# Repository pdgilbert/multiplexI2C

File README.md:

# multiplexI2C
Eight 4-position screw connectors on multiplexed on I2C with PCA9548A. 
This allows connecting 8 I2C sensors such as AHT10 (on module boards) using 
low voltage 4-wire cable.

##  Status: Working Prototype.

## Summary

Kicad project WIP.

PCB design to connect multiple (up to 8) I2C sensors (eg. AHT20) to a I2C multiplexer
connecting to an MCU. Sensor connectors are  4-pin KF128-2.54-4P generic screw terminals.
Many types of I2C sensors are inexpensive and easily available on module boards, 
but 4-wire cable will typically need to be attached. 

The pcb board has a LoRa radio on a SPI bus which transmits measurement results.
There is also a I2C header for an optional OLED display, intended mainly for debugging.

Related software is in repository https://github.com/pdgilbert/SensorProject_th8.

As of December 2025, this repository has three important branches. (Branch `main` is not 
an important branch but rather a somewhat stable version of the most active
development, which is on the `dev` branch. Both may be removed or reorganized 
in the future.)
 
Branch `blackpill-socket` has two 20-pin sockets arranged for a commonly available 
blackpill module. It has an RFM95 LoRa radio on spi, an I2C pinsocket arrange to plug in 
an SSD module for display, and 8 4-pin terminals multiplexed to connect I2C devices.
The pinsocket arrangement can also be used for jumper-wiring MCUs on other development
boards. Further work on this branch will be limited.
 
Branch `f411-RFM95W-module` has a footprint for a module with an MCU and LoRa radio.
(See repository MCU-LoRa for module details.)
It has a socket for I2C arranged to plug in an SSD module for display, 
and 8 4-pin terminals multiplexed to connect I2C devices. 
As of November 2025 this branch is almost ready to manufacture a prototype.
 
Branch `f411-RFM95W` has an STM32F411 MCU and RFM95W LoRa radio on the board (no module).
It has a socket for I2C arrange to plug in an SSD module for display, 
and 8 4-pin terminals multiplexed to connect I2C devices. 
As of December 2025 this branch is almost ready to manufacture a prototype.

See history further below for regarding status and testing of each branch.

Graphics below will be different on different branches, reflecting the differences above.
The `.png` files below are produced from kicad  in the `3D Viewer`  
with `File > Export Current View as PNG`.

( hints from https://docs.github.com/en/repositories/working-with-files/using-files/working-with-non-code-files#3d-file-viewer )

3D  `.wrl` file opens with Meshlab. Good, full colour. 
The file needs to be load into a viewer (e.g.
https://3dviewer.net/#model=https://github.com/pdgilbert/multiplexI2C/f411-RFM95W/Graphics/multiplexI2C.wrl )
or downloaded and viewed with your own viewer. 
To download go to the file in the Graphics/ directory and click on the file.
Github will try to render this, but fails because it is too large.
Then click on the download raw file icon at the top right. 
The file is produced from kicad  with `File > Export ... >  VRML...`

https://3dviewer.net/#model=https://github.com/pdgilbert/multiplexI2C/blob/f411-RFM95W/Graphics/multiplexI2C.wrl

3D  `.step` file can be loaded by Freecad. 
It can be load into a viewer (e.g. 
https://3dviewer.net/#model=https://github.com/pdgilbert/multiplexI2C/f411-RFM95W/Graphics/multiplexI2C.step)
or downloaded as above for `.wrl`.
The file is produced from kicad  with `File > Export ... >  STEP...`

3D  `.stl` file can be  rendered by Github, Meshlab and Freecad. So far only mono-colour is working. 
It can be load into a viewer (e.g. 
https://3dviewer.net/#model=https://github.com/pdgilbert/multiplexI2C/f411-RFM95W/Graphics/multiplexI2C.stl)
To render by Meshlab or Freecad requires downloading as above for `.wrl`.
The file is best produced by exporting a `.wrl` or `.step` file from kicad and
importing that to Meshlab or Freecad, and then exporting an `.stl` file.
The file can also be produced from kicad  with `File > Export ... >  STEP.../STEP...` but
the result has bad artifacts. The .wrl version is much better than the .stl version.

3D  `.ast` file (ASCII stl) is rendered by Github, according to above link, but files  
larger than 10 MB are too big for GitHub to display. 
The `multiplexI2C.ast` is almost 20MB so this format cannot be used by Github.
It is not rendered by Meshlab.

## History
 
 - `th8-F411` version `0.3.1 2025-12` (branch `f411-RFM95W`) has stm32f411 MCU chip and HopeRF RFM95W.
    This version is switched to ssd on I2C1 and sensors on I2C2, so it is consistent with SensorProject_t16.
    The software has a flag to indicate previous old versions.

 - `th8-F411` version `0.3.1M 2025-12` (branch `f411-RFM95W-module`) has not been manufactured/tested.

 - Version `0.1.1 2025-01` (branch `blackpill-socket`) has pull up resistor added but 
   has not been manufactured/tested. This version has ssd on I2C2 and sensors on I2C1.

 - Version `0.1.0 2024-09` (branch `blackpill-socket`) needs manual addition of a pull up 
   resistor to nss of the RFM95W radio module, MCU pin A4. 
   With this modification it works with `blackpill` `stm32f401` or `stm32f411` inserted,
   using AHT10 and AHT20 sensors. With jumper wiring it has also been used to test a WeAct 
   Studio STM32474G474 board.  This version has ssd on I2C2 and sensors on I2C1.
   See notes re testing in the software repository.

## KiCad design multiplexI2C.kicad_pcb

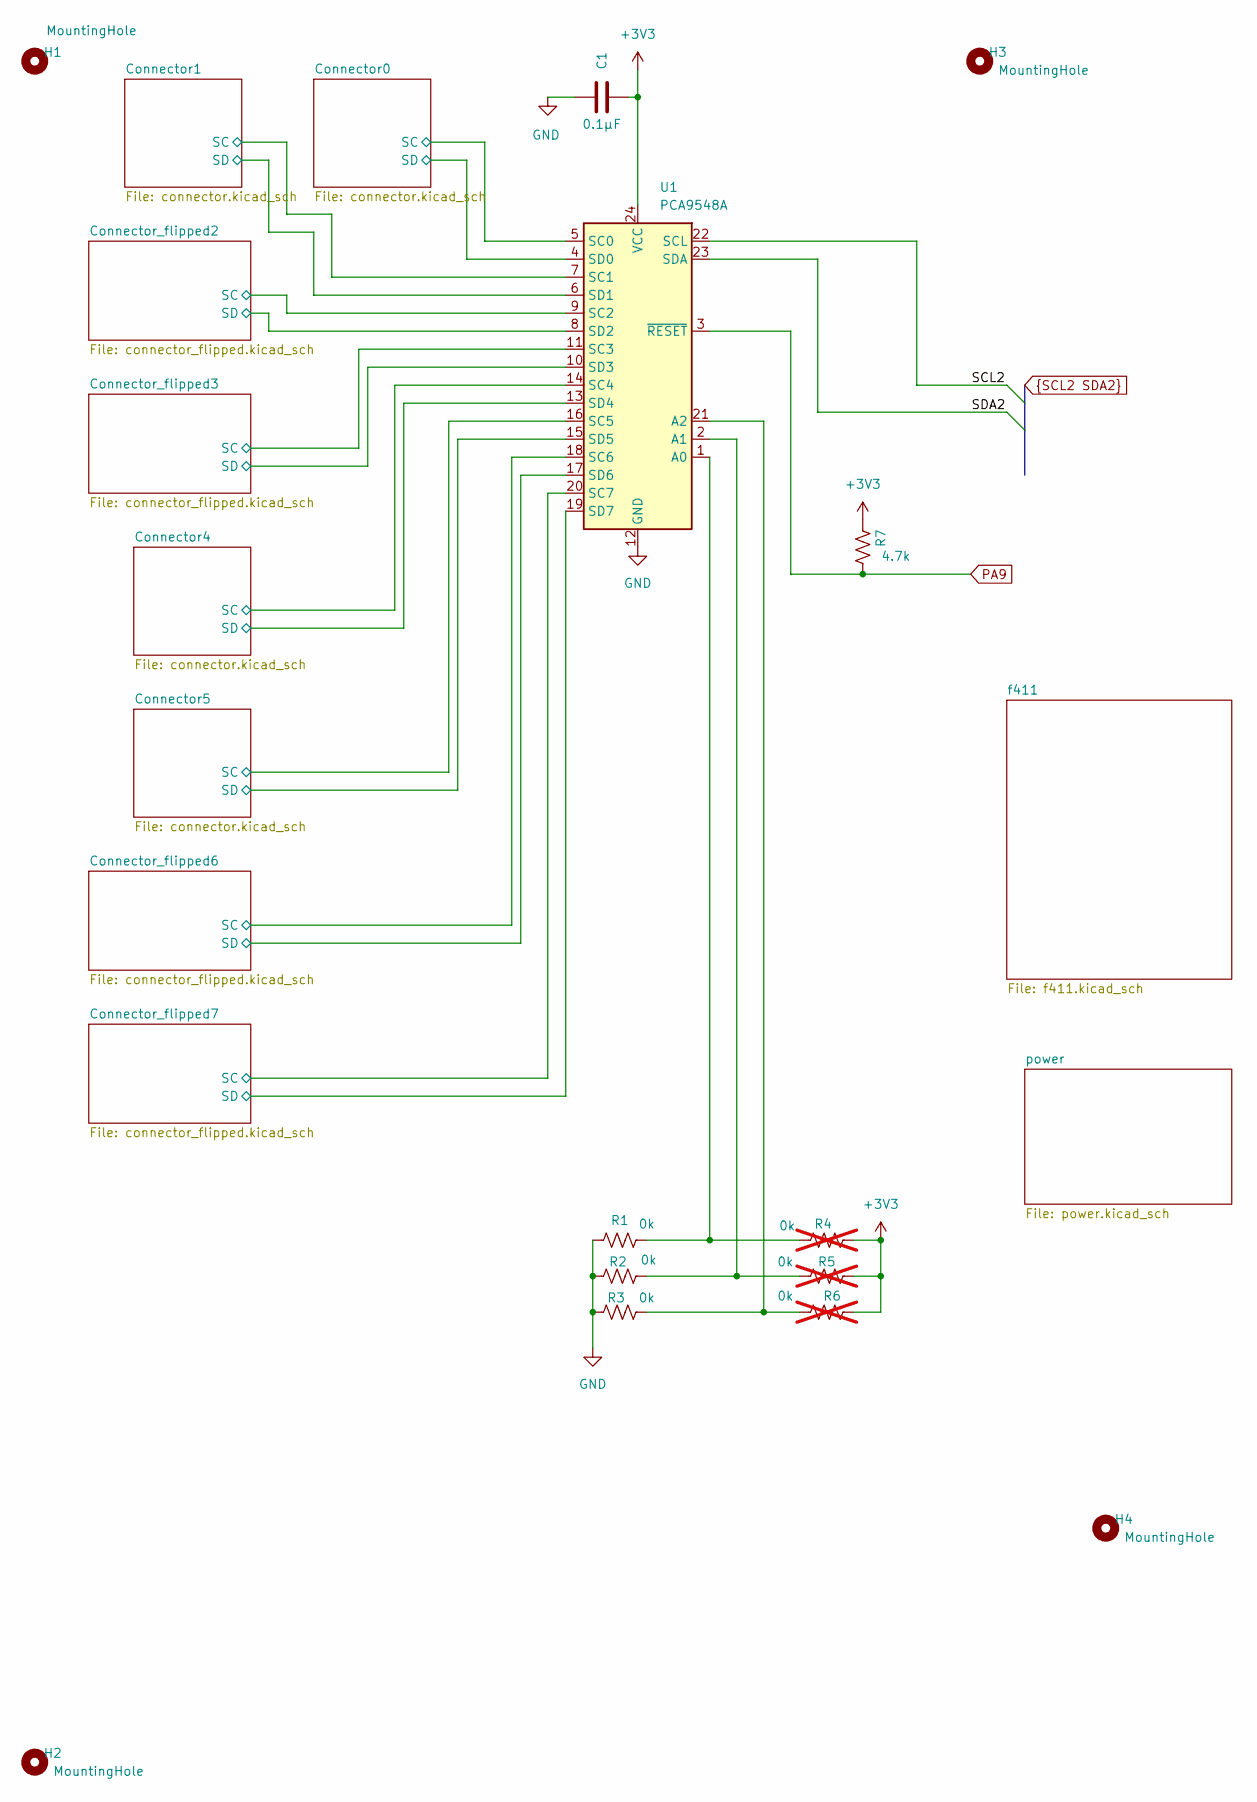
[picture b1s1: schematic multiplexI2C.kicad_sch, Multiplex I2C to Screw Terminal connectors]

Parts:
C1: 0.1µF; C_0402_1005Metric
H1, H2, H3, H4: MountingHole; MountingHole_2.2mm_M2_ISO7380_Pad
R1, R2, R3: 0k; R_0402_1005Metric
R4, R5, R6: 0k; R_0402_1005Metric; not fitted
R7: 4.7k; R_0402_1005Metric
U1: PCA9548A; TSSOP-24_4.4x7.8mm_P0.65mm; MfgPart PCA9548APW

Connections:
+3V3: C1.1, R4.1, R5.1, R6.1, R7.1, U1.24 (VCC); also elsewhere on the board
/Connector0/SC: U1.5 (SC0); also elsewhere on the board
/Connector0/SD: U1.4 (SD0); also elsewhere on the board
/Connector1/SC: U1.7 (SC1); also elsewhere on the board
/Connector1/SD: U1.6 (SD1); also elsewhere on the board
/Connector4/SC: U1.14 (SC4); also elsewhere on the board
/Connector4/SD: U1.13 (SD4); also elsewhere on the board
/Connector5/SC: U1.16 (SC5); also elsewhere on the board
/Connector5/SD: U1.15 (SD5); also elsewhere on the board
/Connector_flipped2/SC: U1.9 (SC2); also elsewhere on the board
/Connector_flipped2/SD: U1.8 (SD2); also elsewhere on the board
/Connector_flipped3/SC: U1.11 (SC3); also elsewhere on the board
/Connector_flipped3/SD: U1.10 (SD3); also elsewhere on the board
/Connector_flipped6/SC: U1.18 (SC6); also elsewhere on the board
/Connector_flipped6/SD: U1.17 (SD6); also elsewhere on the board
/Connector_flipped7/SC: U1.20 (SC7); also elsewhere on the board
/Connector_flipped7/SD: U1.19 (SD7); also elsewhere on the board
GND: C1.2, R1.2, R2.2, R3.2, U1.12 (GND); also elsewhere on the board
unnamed: R1.1, R4.2, U1.1 (A0)
unnamed: R2.1, R5.2, U1.2 (A1)
unnamed: R3.1, R6.2, U1.21 (A2)
PA9: R7.2, U1.3 (~RESET); also elsewhere on the board
SCL2: U1.22 (SCL); also elsewhere on the board
SDA2: U1.23 (SDA); also elsewhere on the board

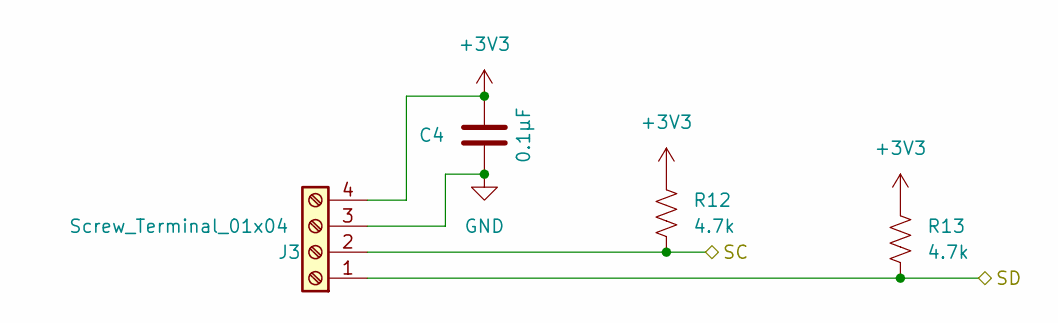
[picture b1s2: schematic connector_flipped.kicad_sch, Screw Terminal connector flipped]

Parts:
C4: 0.1µF; C_0402_1005Metric
J3: Screw_Terminal_01x04; TerminalBlock_Phoenix_MPT-0,5-4-2.54_1x04_P2.54mm_Horizontal; MfgPart KF128-2.54-4P
R12, R13: 4.7k; R_0402_1005Metric

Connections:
+3V3: C4.1, J3.4, R12.1, R13.1; also elsewhere on the board
/Connector_flipped2/SC: J3.2, R12.2; also elsewhere on the board
/Connector_flipped2/SD: J3.1, R13.2; also elsewhere on the board
GND: C4.2, J3.3; also elsewhere on the board

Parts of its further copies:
C5, C8, C9: 0.1µF; C_0402_1005Metric
J4, J7, J8: Screw_Terminal_01x04; TerminalBlock_Phoenix_MPT-0,5-4-2.54_1x04_P2.54mm_Horizontal; MfgPart KF128-2.54-4P
R14, R15, R20, R21, R22, R23: 4.7k; R_0402_1005Metric

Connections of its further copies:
+3V3: C5.1, C8.1, C9.1, J4.4, J7.4, J8.4, R14.1, R15.1, R20.1, R21.1, R22.1, R23.1; also elsewhere on the board
/Connector_flipped3/SC: J4.2, R14.2; also elsewhere on the board
/Connector_flipped3/SD: J4.1, R15.2; also elsewhere on the board
/Connector_flipped6/SC: J7.2, R20.2; also elsewhere on the board
/Connector_flipped6/SD: J7.1, R21.2; also elsewhere on the board
/Connector_flipped7/SC: J8.2, R22.2; also elsewhere on the board
/Connector_flipped7/SD: J8.1, R23.2; also elsewhere on the board
GND: C5.2, C8.2, C9.2, J4.3, J7.3, J8.3; also elsewhere on the board

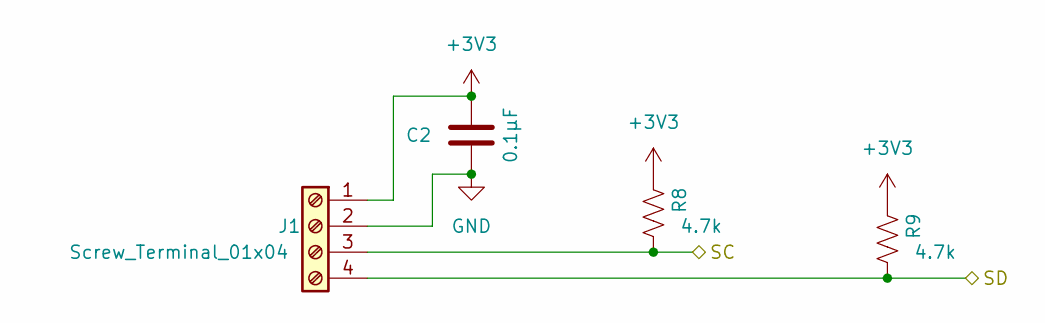
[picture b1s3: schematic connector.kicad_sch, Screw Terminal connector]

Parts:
C2: 0.1µF; C_0402_1005Metric
J1: Screw_Terminal_01x04; TerminalBlock_Phoenix_MPT-0,5-4-2.54_1x04_P2.54mm_Horizontal; MfgPart KF128-2.54-4P
R8, R9: 4.7k; R_0402_1005Metric

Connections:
+3V3: C2.1, J1.1, R8.1, R9.1; also elsewhere on the board
/Connector0/SC: J1.3, R8.2; also elsewhere on the board
/Connector0/SD: J1.4, R9.2; also elsewhere on the board
GND: C2.2, J1.2; also elsewhere on the board

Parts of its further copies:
C3, C6, C7: 0.1µF; C_0402_1005Metric
J2, J5, J6: Screw_Terminal_01x04; TerminalBlock_Phoenix_MPT-0,5-4-2.54_1x04_P2.54mm_Horizontal; MfgPart KF128-2.54-4P
R10, R11, R16, R17, R18, R19: 4.7k; R_0402_1005Metric

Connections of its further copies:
+3V3: C3.1, C6.1, C7.1, J2.1, J5.1, J6.1, R10.1, R11.1, R16.1, R17.1, R18.1, R19.1; also elsewhere on the board
/Connector1/SC: J2.3, R10.2; also elsewhere on the board
/Connector1/SD: J2.4, R11.2; also elsewhere on the board
/Connector4/SC: J5.3, R16.2; also elsewhere on the board
/Connector4/SD: J5.4, R17.2; also elsewhere on the board
/Connector5/SC: J6.3, R18.2; also elsewhere on the board
/Connector5/SD: J6.4, R19.2; also elsewhere on the board
GND: C3.2, C6.2, C7.2, J2.2, J5.2, J6.2; also elsewhere on the board

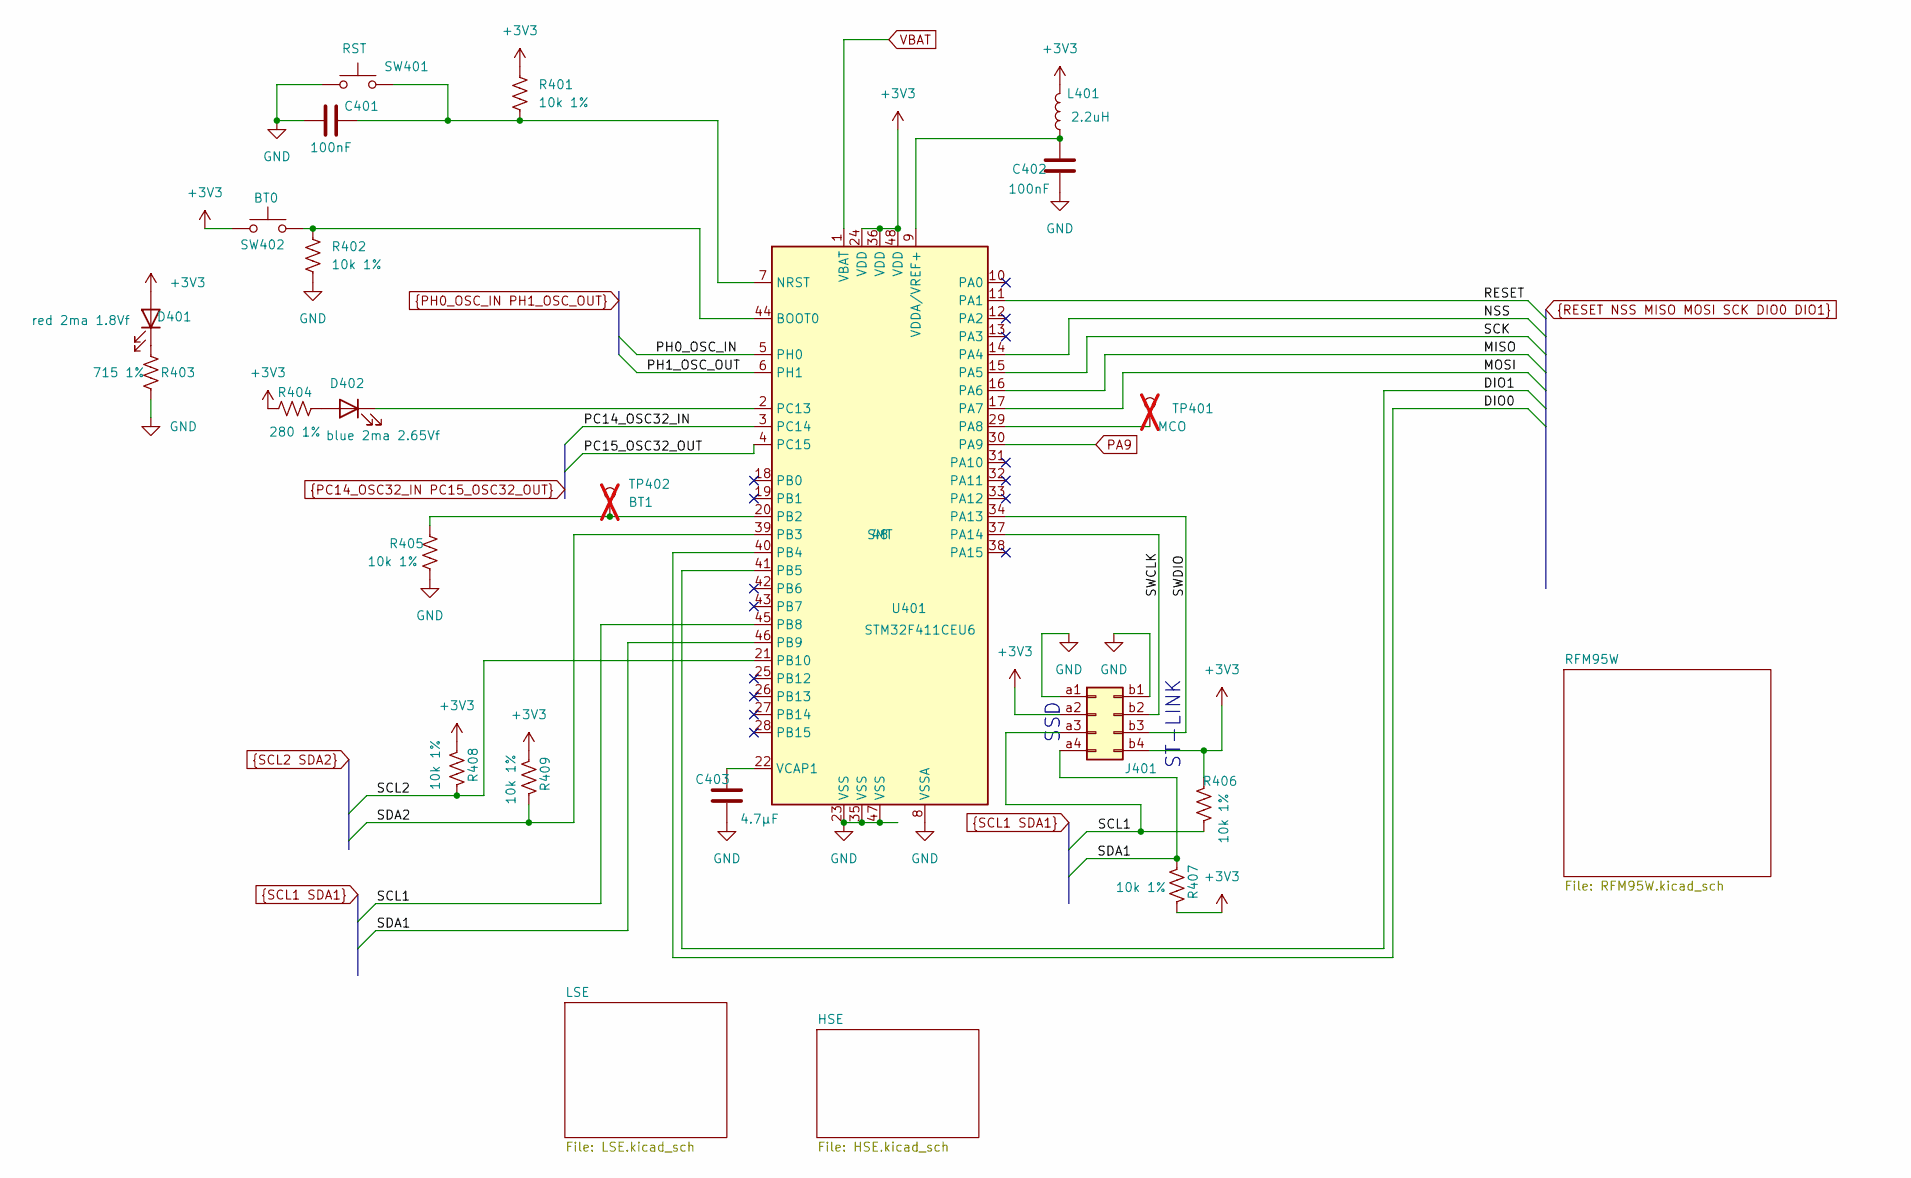
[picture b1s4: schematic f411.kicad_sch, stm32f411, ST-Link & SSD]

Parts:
C401, C402: 100nF; C_0402_1005Metric
C403: 4.7µF; C_0402_1005Metric
D401: red 2ma 1.8Vf; LED_0603_1608Metric; MfgPart APT1608LSECK/J3-PRV
D402: blue 2ma 2.65Vf; LED_0603_1608Metric; MfgPart APT1608LVBC/D
J401: Conn_02x04_Top_Bottom; PinSocket_2x04_P2.54mm_Vertical_SMD; MfgPart HC-PM254-5.0H-2x4PS-02A
L401: 2.2uH; L_0402_1005Metric; MfgPart MLZ1005M2R2WT000
R401, R402, R405, R406, R407, R408, R409: 10k 1%; R_0402_1005Metric
R403: 715 1%; R_0402_1005Metric
R404: 280 1%; R_0402_1005Metric
SW401, SW402: SW_Push; SW_SPST_B3U-1000P; MfgPart B3U-1000P
TP401: MCO; TestPoint_Pad_D1.0mm; not fitted
TP402: BT1; TestPoint_Pad_D1.0mm; not fitted
U401: STM32F411CEU6; QFN-48-1EP_7x7mm_P0.5mm_EP5.6x5.6mm; MfgPart STM32F411CEU6

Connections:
+3V3: D401.2 (A), J401.a2, J401.b4, L401.2, R401.1, R404.1, R406.1, R407.2, R408.1, R409.1, SW402.1, U401.24 (VDD), U401.36 (VDD), U401.48 (VDD); also elsewhere on the board
/f411/SWCLK: J401.b2, U401.37 (PA14)
/f411/SWDIO: J401.b3, U401.34 (PA13)
DIO0: U401.40 (PB4); also elsewhere on the board
DIO1: U401.41 (PB5); also elsewhere on the board
GND: C401.1, C402.2, C403.2, J401.a1, J401.b1, R402.2, R403.2, R405.2, SW401.1, U401.8 (VSSA), U401.23 (VSS), U401.35 (VSS), U401.47 (VSS), U401.49 (VSS); also elsewhere on the board
MISO: U401.16 (PA6); also elsewhere on the board
MOSI: U401.17 (PA7); also elsewhere on the board
NSS: U401.14 (PA4); also elsewhere on the board
unnamed: D401.1 (K), R403.1
unnamed: D402.2 (A), R404.2
unnamed: D402.1 (K), U401.2 (PC13)
unnamed: R402.1, SW402.2, U401.44 (BOOT0)
unnamed: C401.2, R401.2, SW401.2, U401.7 (NRST)
unnamed: TP401.1, U401.29 (PA8)
unnamed: R405.1, TP402.1, U401.20 (PB2)
unnamed: C403.1, U401.22 (VCAP1)
unnamed: C402.1, L401.1, U401.9 (VDDA/VREF+)
PA9: U401.30 (PA9); also elsewhere on the board
PC14_OSC32_IN: U401.3 (PC14); also elsewhere on the board
PC15_OSC32_OUT: U401.4 (PC15); also elsewhere on the board
PH0_OSC_IN: U401.5 (PH0); also elsewhere on the board
PH1_OSC_OUT: U401.6 (PH1); also elsewhere on the board
RESET: U401.11 (PA1); also elsewhere on the board
SCK: U401.15 (PA5); also elsewhere on the board
SCL1: J401.a3, R406.2, U401.45 (PB8)
SCL2: R408.2, U401.21 (PB10); also elsewhere on the board
SDA1: J401.a4, R407.1, U401.46 (PB9)
SDA2: R409.2, U401.39 (PB3); also elsewhere on the board
VBAT: U401.1 (VBAT); also elsewhere on the board

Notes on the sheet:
SSD
ST-LINK

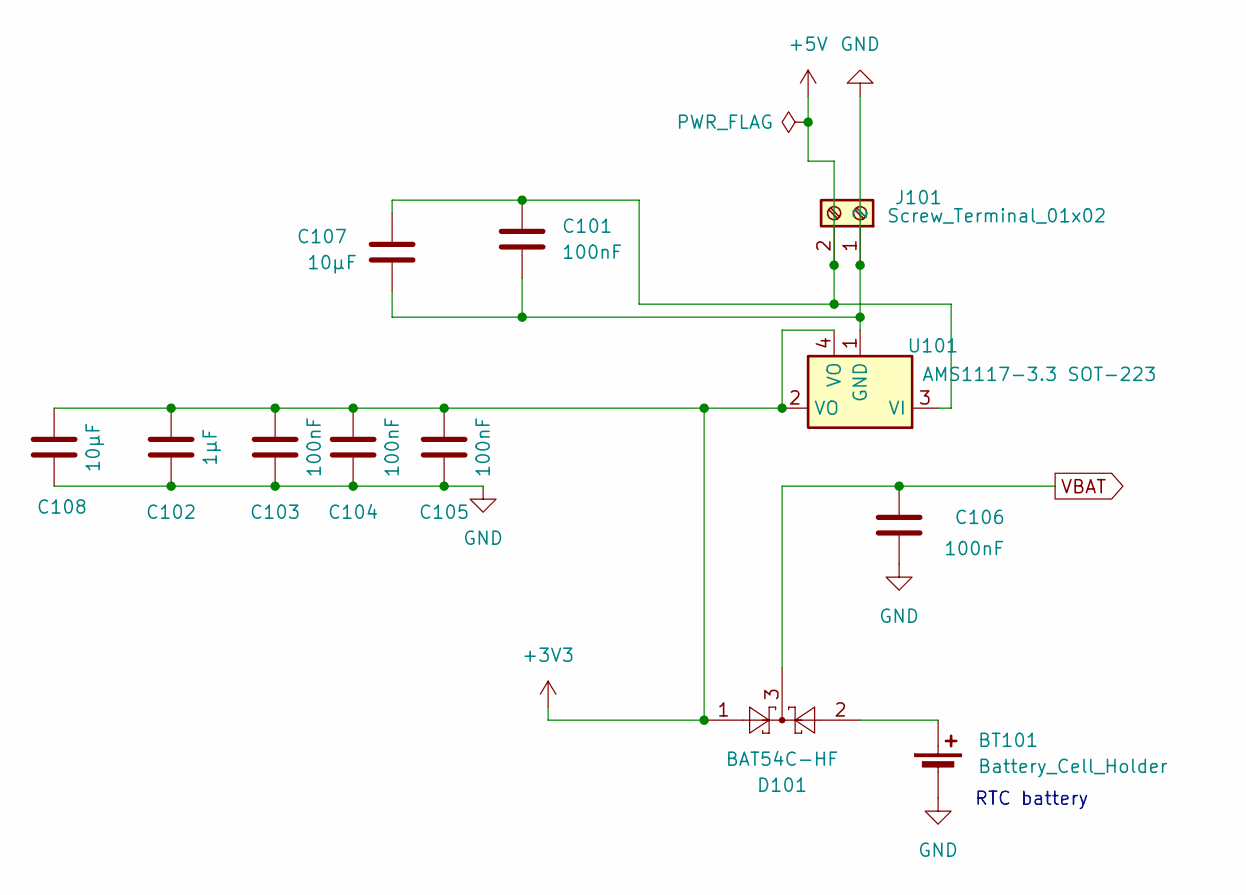
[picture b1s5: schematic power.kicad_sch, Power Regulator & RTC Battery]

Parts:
BT101: Battery_Cell_Holder; BatteryHolder_LINX_BAT-HLD-012-SMT; MfgPart BAT-HLD-012-SMT
C101, C103, C104, C105, C106: 100nF; C_0402_1005Metric
C102: 1µF; C_0402_1005Metric
C107, C108: 10µF; C_0402_1005Metric
D101: BAT54C-HF; SOT-23; MfgPart BAT54C-HF
J101: Screw_Terminal_01x02; TerminalBlock_Phoenix_MPT-0,5-2-2.54_1x02_P2.54mm_Horizontal; MfgPart KF128-2.54-2P
U101: AMS1117-3.3 SOT-223; SOT-223; MfgPart AMS1117-3.3

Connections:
+3V3: C102.1, C103.1, C104.1, C105.1, C108.1, D101.1, U101.2 (VO), U101.4 (VO); also elsewhere on the board
+5V: C101.1, C107.1, J101.2, U101.3 (VI)
GND: BT101.2 (-), C101.2, C102.2, C103.2, C104.2, C105.2, C106.2, C107.2, C108.2, J101.1, U101.1 (GND); also elsewhere on the board
unnamed: BT101.1 (+), D101.2
VBAT: C106.1, D101.3; also elsewhere on the board

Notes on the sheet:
RTC battery

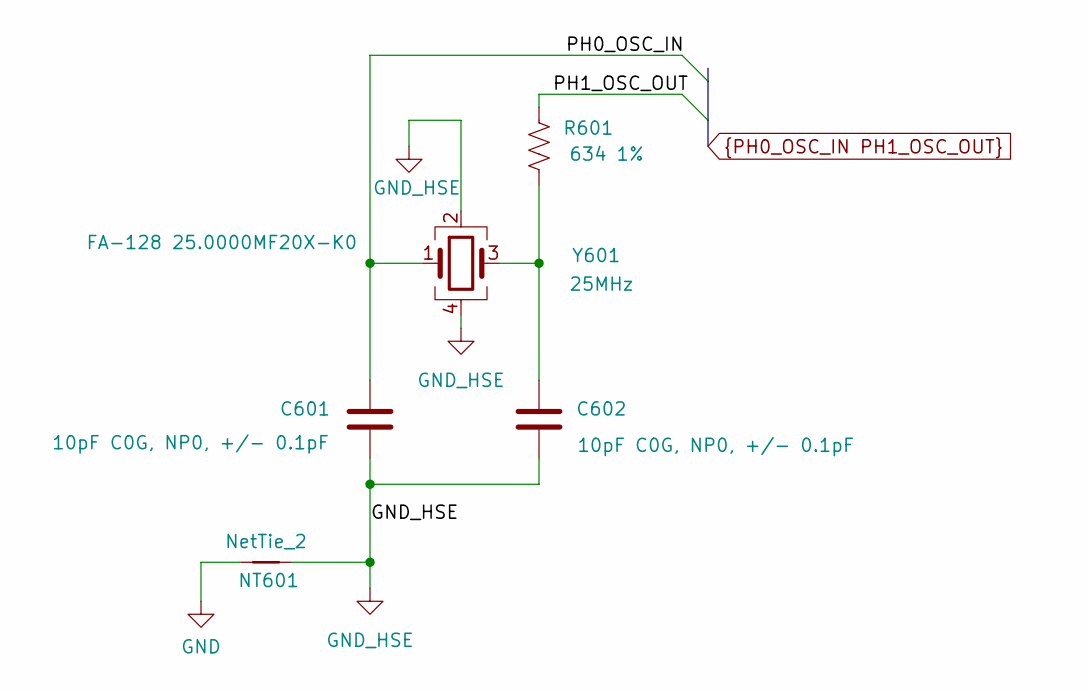
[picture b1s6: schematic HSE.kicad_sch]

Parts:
C601, C602: 10pF C0G, NP0, +/- 0.1pF; C_0402_1005Metric
NT601: NetTie_2; NetTie-2_SMD_Pad0.5mm
R601: 634 1%; R_0402_1005Metric
Y601: 25MHz; Crystal_SMD_2016-4Pin_2.0x1.6mm; MfgPart FA-128 25.0000MF20X-K0

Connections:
GND: NT601.1; also elsewhere on the board
GND_HSE: C601.1, C602.1, NT601.2, Y601.2, Y601.4
unnamed: C602.2, R601.2, Y601.3
PH0_OSC_IN: C601.2, Y601.1; also elsewhere on the board
PH1_OSC_OUT: R601.1; also elsewhere on the board

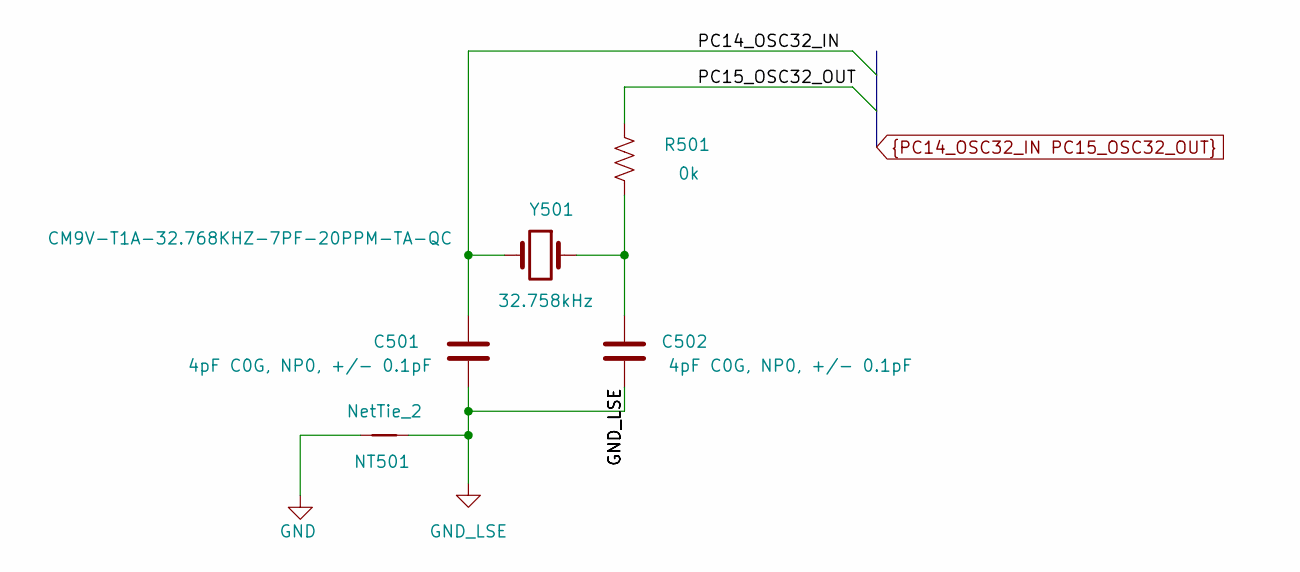
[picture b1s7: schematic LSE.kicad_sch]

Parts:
C501, C502: 4pF C0G, NP0, +/- 0.1pF; C_0402_1005Metric
NT501: NetTie_2; NetTie-2_SMD_Pad0.5mm
R501: 0k; R_0402_1005Metric
Y501: 32.758kHz; Crystal_SMD_MicroCrystal_CM9V-T1A-2Pin_1.6x1.0mm; MfgPart CM9V-T1A-32.768KHZ-7PF-20PPM-TA-QC

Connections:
GND: NT501.1; also elsewhere on the board
GND_LSE: C501.1, C502.1, NT501.2
unnamed: C502.2, R501.2, Y501.1
PC14_OSC32_IN: C501.2, Y501.2; also elsewhere on the board
PC15_OSC32_OUT: R501.1; also elsewhere on the board

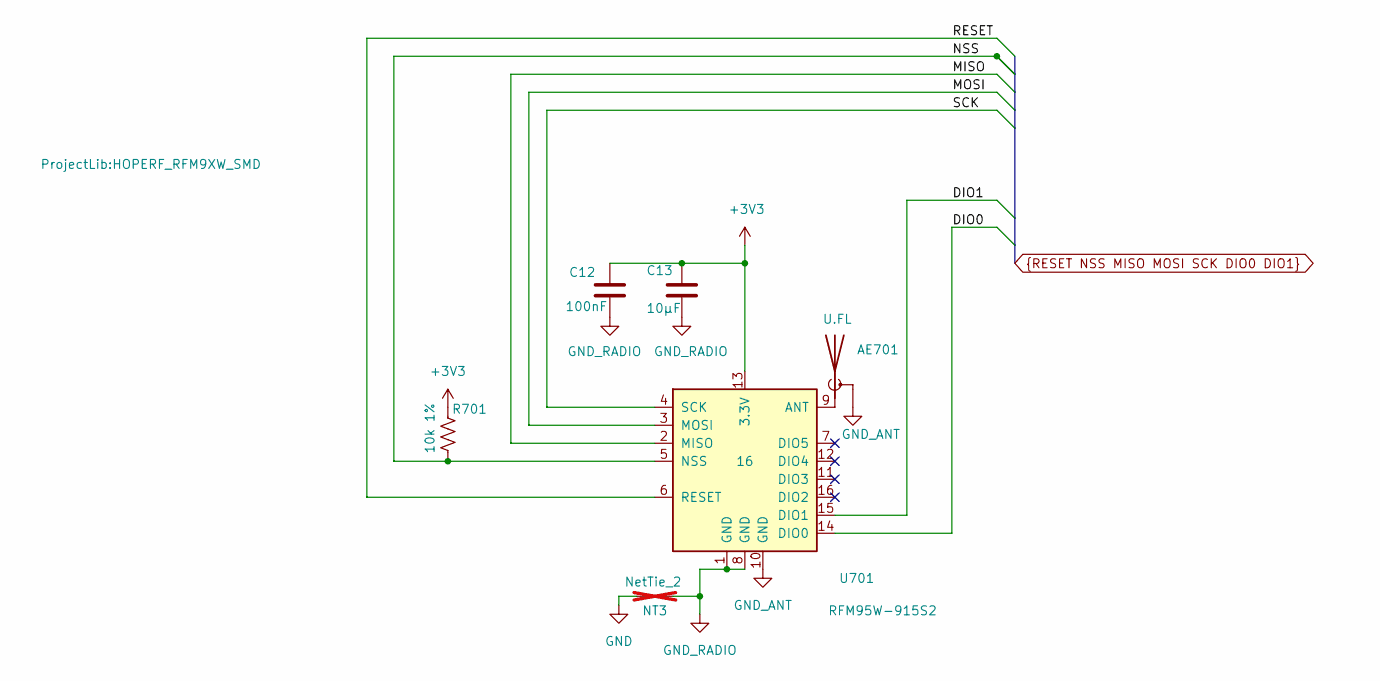
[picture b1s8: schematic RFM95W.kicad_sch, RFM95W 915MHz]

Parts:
AE701: U.FL; U.FL_Molex_MCRF_73412-0110_Vertical; MfgPart U.FL-R-SMT-K(800)
C12: 100nF; C_0402_1005Metric
C13: 10µF; C_0402_1005Metric
NT3: NetTie_2; NetTie-2_SMD_Pad0.5mm; not fitted
R701: 10k 1%; R_0402_1005Metric
U701: RFM95W-915S2; HOPERF_RFM9XW_SMD; MfgPart RFM95W-915S2

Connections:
+3V3: C12.1, C13.1, R701.1, U701.13 (3.3V); also elsewhere on the board
DIO0: U701.14 (DIO0); also elsewhere on the board
DIO1: U701.15 (DIO1); also elsewhere on the board
GND: NT3.1; also elsewhere on the board
GND_ANT: AE701.2 (Shield), U701.10 (GND)
GND_RADIO: C12.2, C13.2, NT3.2, U701.1 (GND), U701.8 (GND)
MISO: U701.2 (MISO); also elsewhere on the board
MOSI: U701.3 (MOSI); also elsewhere on the board
NSS: R701.2, U701.5 (NSS); also elsewhere on the board
unnamed: AE701.1 (A), U701.9 (ANT)
RESET: U701.6 (RESET); also elsewhere on the board
SCK: U701.4 (SCK); also elsewhere on the board

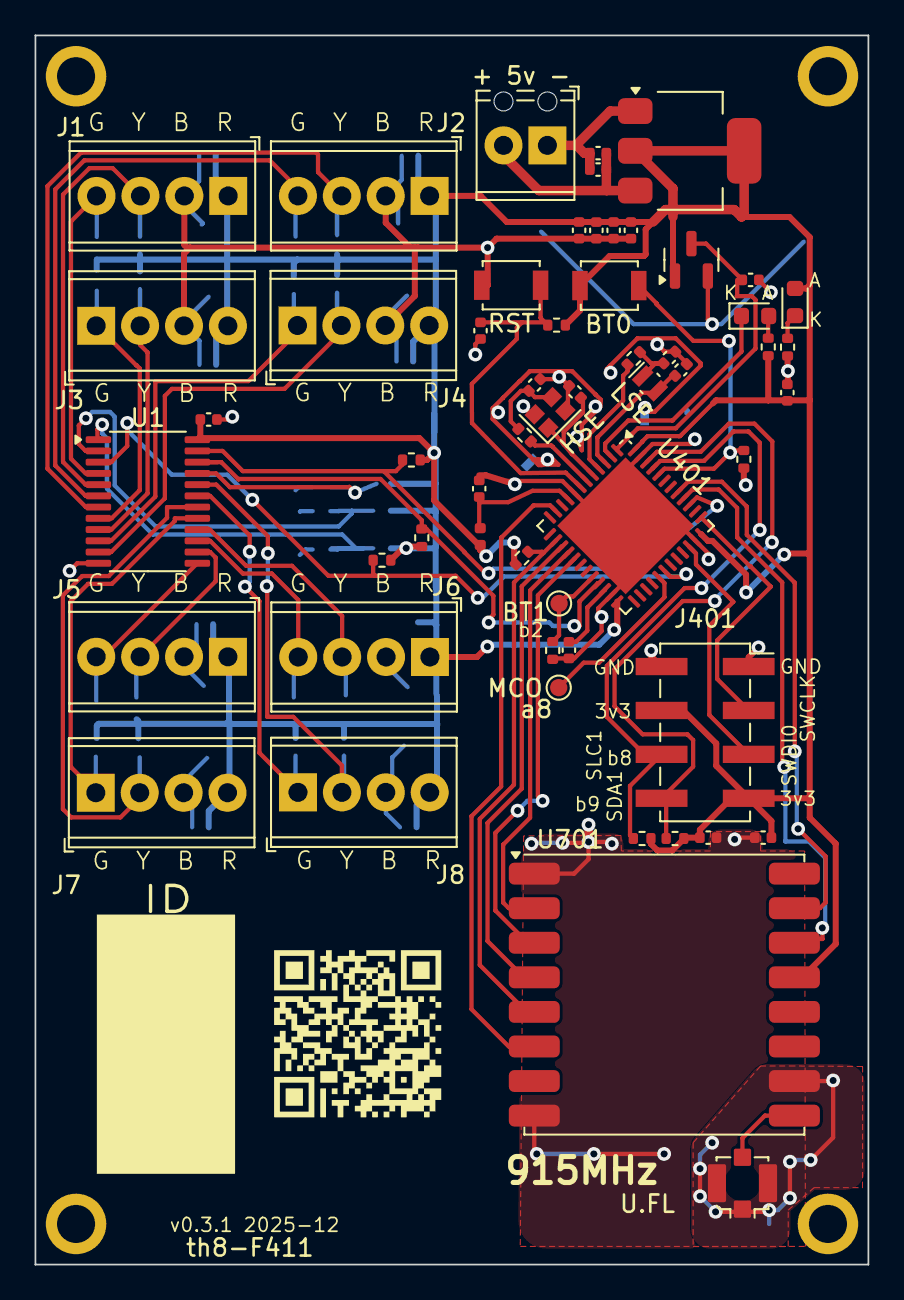
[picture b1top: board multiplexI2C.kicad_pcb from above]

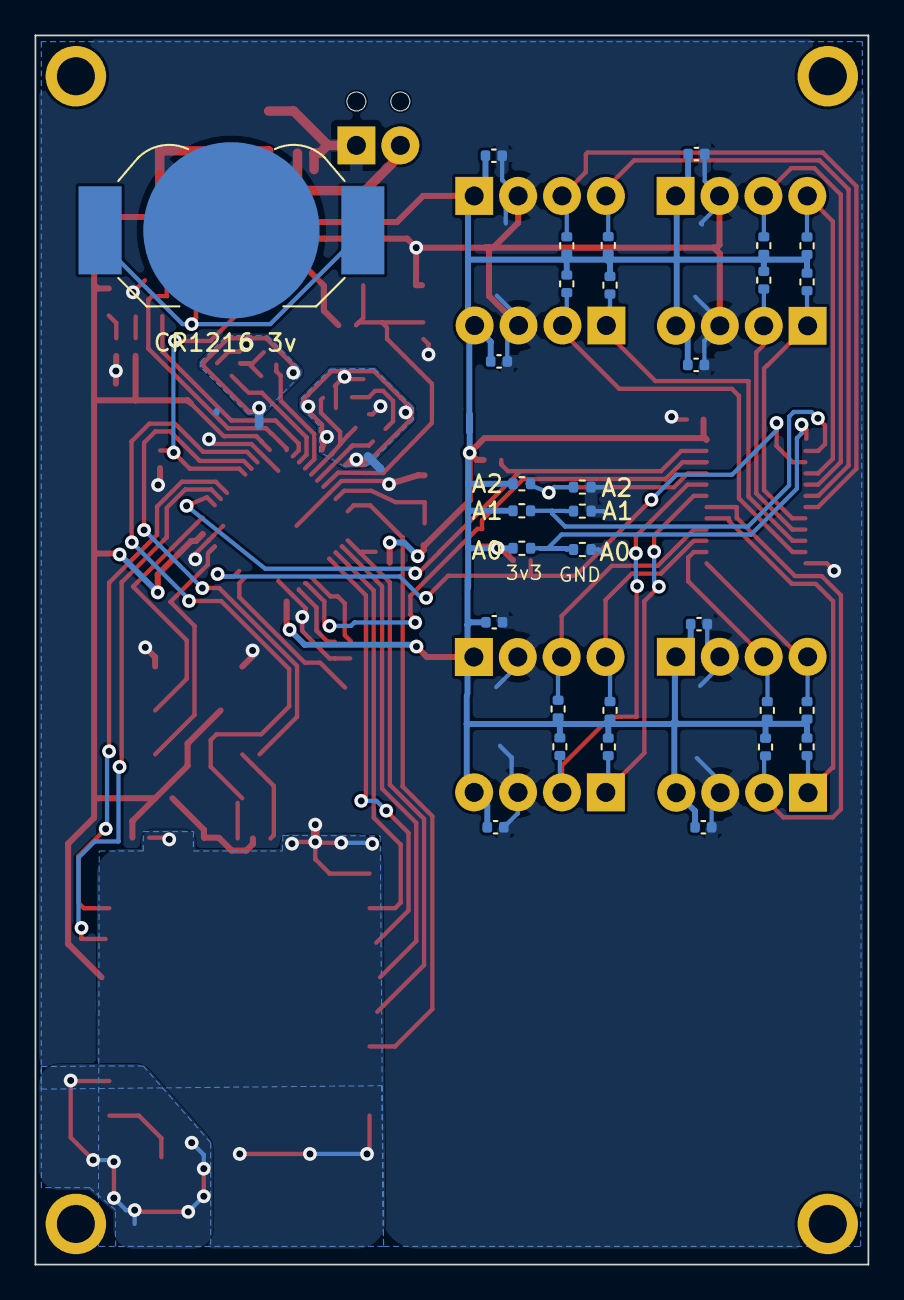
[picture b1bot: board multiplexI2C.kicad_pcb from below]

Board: 2 copper layers, 48.2 x 71.1 mm, 96 parts (33 on the bottom side), 58 nets.

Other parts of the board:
G1: LOGO; SensorProject_QR
G2: LOGO; SensorProject_IDblock

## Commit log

2024-07-28 add first draft, schematic. PCB still old from copied template.
2024-07-30 schematic first draft done, starting to populate pcb.
2024-08-04 ERC and DRC warnings but not erros. Needs some layout adjustments.
2024-08-06 no ELC or DRC errors. Still cleaning up warnings. Switched to SW_DIP for PCA9548 address.
2024-08-07 roughly complete, no errors or warnings.
2024-08-07 adding Graphics to README.
2024-08-07 trying to view 3D from README.
2024-08-07 still trying to view 3D from README.
2024-08-16 put masks on takeoffPads and other ongoing cleanup.
2024-08-16 playing with 3D graphics file in README.
2024-08-19 clean up symbol fields
2024-08-20 passing checks with TCA9548A in pass. Ongoingg cleanup.
2024-08-20 converted to TCA9548A, cleaned up and regenerated graphics. No ERC or DRC errors.
2024-08-20 added TCA footprint to ProjectLib. Minor cleanup and fiddling with README graphics.
2024-08-20 minor cleanup of notes.
2024-08-21 added header for ssd1306.
2024-08-21 ssd1306 header cleanup.
2024-08-24 replaced address switch with R0 changeable by solder.
2024-08-24 replaced address switch with R0 changeable by solder. Cleanup.
2024-08-24 new graphics
2024-08-25 squeezed connectors closer together to make room for sx127x module.
2024-08-29 added RFM95W pad for sx127x, unpopulated.
2024-08-29 added fill zone behind radio and other cleanup.
2024-08-30 adding radio-sx127x files, revised graphics and notes.
2024-09-04 e220 schematic needs work, and proper DIO connections. Switching back to radio-sx127.
2024-09-04 renamed radio-sx127x.kicad_sch to RFM95W.kicad_sch
2024-09-07 some cleanup. About to split two lra module branches.
2024-09-07 DRC ot errors. 3D not showing U2.
2024-09-07 added antenna connector.
2024-09-08 added antenna. No 3d yet.
2024-09-08 Working on 3dmodels. ssd header messed up.
2024-09-08 ssd header fixed. Ongoing work on 3d models.
2024-09-08 3D working but antenna is not yet good. ERC and DRC no errors. BOM needs adjustments.
2024-09-10 cleaning up details forbetter BOM generator.
2024-09-15 as ordered 2024-09 with minor changes for part availability.
2025-01-06 added 10k pullup on NSS.
2025-01-07 update README.
2025-09-07 minor doc cleanup.
2025-09-07 ongoing conversion to put f411 on board rather than pinsocket.
2025-09-07 ongoing add of MCU, etc.
2025-09-07 ongoing...
2025-09-08 symbols an footprints added for f411 change. ERC passes.
2025-09-08 ongoing
2025-11-10 adding MCU, ongoing.
2025-11-22 th8-f411 with castellated MCU-LoRa. DRC clean, ERC with some warnings.
2025-11-23 saved with kicad version update.
2025-11-25 four sensor connectors flipped to the way they should be installed.
2025-11-25 changed single 10k pull-up to 4.7k like others. Renumbered components to fill numbering gaps.
2025-11-25 cleaned up fab layer annotation.
2025-11-27 3d showing well with MCU-LoRa step model. Clean up of silkscreen and fab layers. Small movement of some components so silkscreen label placement is better.
2025-11-28 Minor README and ProjectNotes updates.
2025-11-29 more cleanup.
2025-11-29 renamed file for MCU-LoRa sheet, so the filename and sheetname match.
2025-11-29 ongoing.
2025-12-01 schematic good. Footprint placement ongoing.
2025-12-03 ERC and DRC good. Needs fab layer cleanup.
2025-12-03 adjusted copper zones and mounting holes for better setback from edge. Fab layers cleanup and some documentation cleanup.
2025-12-03 minor README adjustment.
2025-12-03 duplicating README and Notes on branches.
2025-12-04 sync doc.
2025-12-04 added QR and IDblock. moved gnd zone and mount holes to give better clearance from board edge.
2025-12-04 update graphics and adjusted README for online wrl viewer.
2025-12-05 ongoing cleanup for submit.
2026-04-02 th8-F411 2025-12 plus some cleanup post manufacturing.
2026-04-09 superficial adjustments for warnings found by kicaad 10.
